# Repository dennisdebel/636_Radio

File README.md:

# 636_Radio
Modern replica of China's first domestically produced single transistor AM radio

## PCB / Gerbers
This replica is deisgned in a way it is easy to solder for beginners on a pcb made 'at home'. This means, optimized for single side copper clad boards.
The pcb is designed in KiCad. If you want to produce this board directly, the latest 'gerber' files can be found [here](https://github.com/dennisdebel/636_Radio/tree/main/gerbers-may6-2024)

## Case
The [case](https://github.com/dennisdebel/636_Radio/tree/main/636-radio-case) and tuner button are designed in OpenSCAD based on the excellent [YAPP_box](https://github.com/mrWheel/YAPP_Box) (Yet Another Parametric Projectbox generator). Find the printable box [here](https://github.com/dennisdebel/636_Radio/blob/main/636-radio-case/636-radio-case-2.1.stl)

## Bill Of Materials
The bill of materials and interactive assembly guide can be found [here](bom/ibom.html). Please ignore the footprint names of some of the components, namely C1 (this is a variable capacitor) and L1 (AM ferrite antenna).

Let me know if you have any issues, suggestions and/or questions!

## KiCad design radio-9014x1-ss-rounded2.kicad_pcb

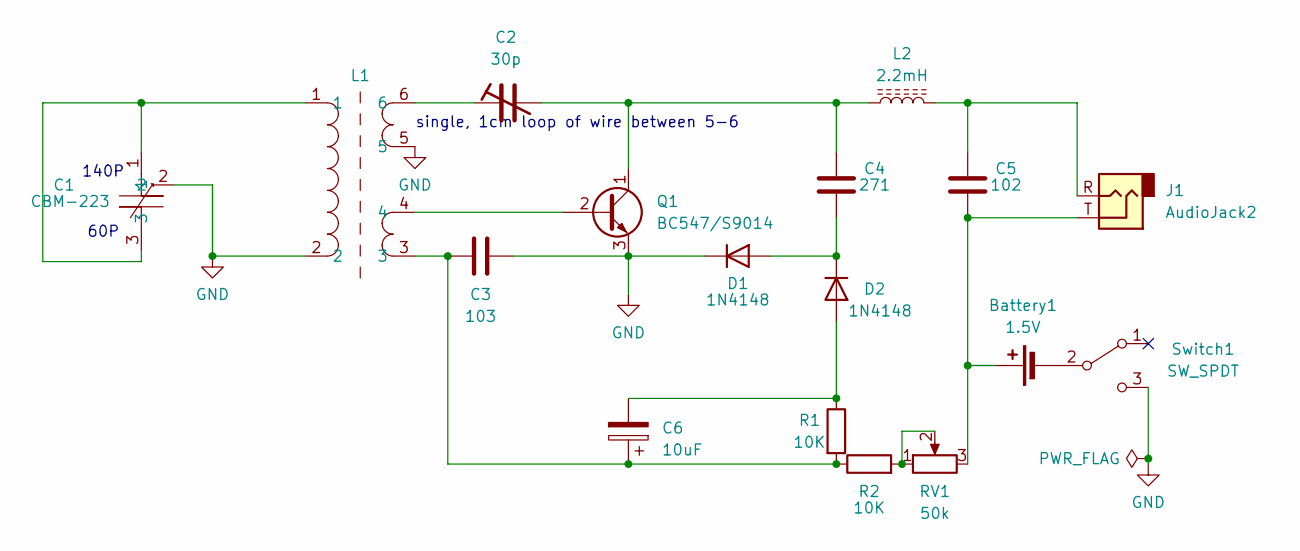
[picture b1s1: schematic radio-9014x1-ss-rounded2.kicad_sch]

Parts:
Battery1: 1.5V; BatteryHolder_Keystone_2460_1xAA
C1: CBM-223; RotaryEncoder_Bourns_Vertical_PEC12R-3x17F-Sxxxx
C2: 30p; VCAP_GKGXXX15_SGM
C3: 103; C_Disc_D4.3mm_W1.9mm_P5.00mm
C4: 271; C_Disc_D4.3mm_W1.9mm_P5.00mm
C5: 102; C_Disc_D4.3mm_W1.9mm_P5.00mm
C6: 10uF; CP_Radial_D5.0mm_P2.50mm
D1, D2: 1N4148; D_DO-35_SOD27_P7.62mm_Horizontal
J1: AudioJack2; Jack_3.5mm_CUI_SJ1-3525N_Horizontal
L1: L_CommonMode_Toroid_Vertical_L43.2mm_W22.9mm_Px17.78mm_Py30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
L2: 2.2mH; LairdTech_28C0236-0JW-10
Q1: BC547/S9014; TO-92_Inline_Wide
R1, R2: 10K; R_Axial_DIN0207_L6.3mm_D2.5mm_P10.16mm_Horizontal
RV1: 50k; TRIM_3306F-1-503
Switch1: SW_SPDT; SW_CuK_OS102011MA1QN1_SPDT_Angled

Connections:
GND: C1.2, C3.1, D1.1 (K), L1.2, L1.5, Q1.3 (E), Switch1.3 (C)
unnamed: Battery1.1 (+), C5.1, J1.T, RV1.3
unnamed: Battery1.2 (-), Switch1.2 (B)
unnamed: C1.1, C1.3, L1.1
unnamed: C2.1, L1.6
unnamed: C3.2, C6.1, L1.3, R1.2, R2.1
unnamed: C5.2, J1.R, L2.2
unnamed: C4.1, D1.2 (A), D2.1 (K)
unnamed: C6.2, D2.2 (A), R1.1
unnamed: L1.4, Q1.2 (B)
unnamed: C2.2, C4.2, L2.1, Q1.1 (C)
unnamed: R2.2, RV1.1, RV1.2

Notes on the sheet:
140P
60P
single, 1cm loop of wire between 5-6

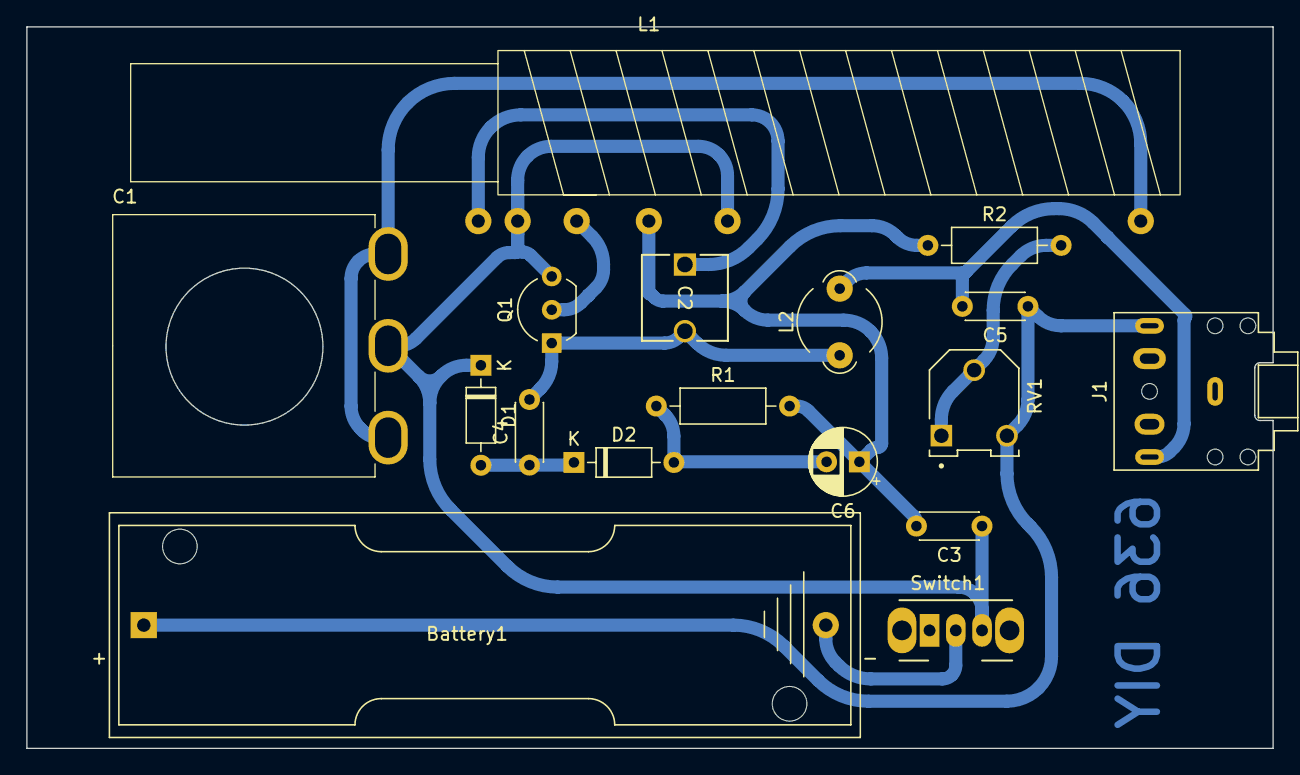
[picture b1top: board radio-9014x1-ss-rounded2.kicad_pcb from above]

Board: 2 copper layers, 95.0 x 55.0 mm, 17 parts (0 on the bottom side), 12 nets.

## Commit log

2023-12-07 added kicad project files
2023-12-07 Added reference image for 'final' version
2024-01-08 Easier soldering
    Edited transistor footprint to the 'wide' variety for easier soldering
2024-04-19 added files for 3d printable case
2024-04-22 fine tuned case designs
2024-04-23 updated pcb
    wider transistor footprint for easier soldering
2024-04-23 added production gerbers
    If manually cnc this, select a copper bottom template
2024-04-27 added slack
    on ridge and standoffs (give some room to the on/off switch)
2024-05-06 Easier hand soldering
2024-05-06 Updated case
    To better facilitate on/off button
2024-05-06 added final image
2024-05-06 Added assembly instructions
2024-05-06 Added some notes on the BOM
